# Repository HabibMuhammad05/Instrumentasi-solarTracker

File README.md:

# Solar Tracker and Monitoring System

This project is a solar tracking and monitoring system designed to adjust the position of a solar panel based on light intensity and monitor several electrical and environmental parameters.

The system uses two microcontrollers, an Arduino Nano and an ESP8266. The Arduino Nano handles the tracking mechanism, sensor readings, and output controls, while the ESP8266 manages serial communication, Wi-Fi connectivity, data transmission, and the OLED display.

The repository contains several program versions and test examples from the development process. The latest program set available in this repository is **Arduino Nano V2.1** and **ESP8266 V2.2**.

## Main Features

- Automatic solar panel positioning based on four LDR sensors.
- Manual positioning control through serial commands.
- Horizontal and vertical panel movement using two servo motors.
- Solar panel voltage, current, and power monitoring.
- Battery voltage and estimated battery level monitoring.
- Panel temperature measurement.
- Control of two PJU lighting outputs.
- LED output effects for tree lighting.
- OLED display for system status and monitoring information.
- Wi-Fi connection and HTTP data transmission to a configured server.
- Serial communication between the Arduino Nano and ESP8266.

## System Overview

The system is divided into two main parts.

### Arduino Nano

The Arduino Nano is responsible for the hardware control and data acquisition:

- Reads four LDR sensors to determine the direction of the strongest light.
- Adjusts the solar panel position through pan and tilt servo motors.
- Supports automatic and manual tracking modes.
- Measures solar panel voltage and current.
- Calculates solar panel power.
- Reads battery voltage and estimates its percentage.
- Reads panel temperature using an LM35 sensor.
- Controls two PJU outputs and four additional LED outputs.
- Sends monitoring data to the ESP8266 and receives control data through serial communication.

### ESP8266 (Wemos D1)

The ESP8266 handles communication and monitoring functions:

- Exchanges telemetry and control data with the Arduino Nano through serial communication.
- Connects to a Wi-Fi network.
- Sends monitoring data to a configured HTTP server in JSON format.
- Displays system information through a 128×64 OLED display.

## Hardware Overview

The main hardware components used in the project include:

- Arduino Nano.
- ESP8266 / Wemos D1 mini.
- Solar panel.
- Four LDR sensors.
- Two servo motors for horizontal and vertical movement.
- Voltage sensing circuits for the solar panel and battery.
- Current sensor for solar panel current measurement.
- LM35 temperature sensor.
- 128×64 OLED display using the SSD1306 controller.
- PJU lighting outputs and additional LED indicators.
- Power supply, battery, wiring, and supporting electronic components.
- Custom PCB for system integration.

Component specifications and wiring may vary depending on the hardware assembly. Refer to the schematic, PCB files, and pin definitions included in the repository before building or modifying the system.

## Software and Libraries

The programs are developed using the Arduino IDE.

The main libraries used in the latest program set include:

- **Servo2** – controls the pan and tilt servo motors on the Arduino Nano.
- **SoftwareSerial** – provides serial communication between the Arduino Nano and ESP8266.
- **U8g2** – controls the SSD1306 OLED display.
- **ESP8266WiFi** – manages the ESP8266 Wi-Fi connection.
- **ESP8266HTTPClient** – handles HTTP requests to the server.
- **ArduinoJson** – formats monitoring data into JSON.

Some earlier programs and examples use additional libraries. Install the libraries required by the specific sketch before compiling it.

## Repository Contents

The repository contains several program versions and supporting files:

| Folder | Description |
|---|---|
| `ArduinoNano_DualComms` | Arduino Nano program for an earlier dual-communication development version. |
| `ArduinoNano_FixCode_Comms` | Revised Arduino Nano program with separated control and monitoring functions. |
| `ArduinoNano_V2.1_FixCode_Comms` | Latest Arduino Nano program included in this repository. |
| `Esp8266_DualComms` | ESP8266 program for an earlier dual-communication development version. |
| `Esp8266_FixCode_Comms` | Revised ESP8266 communication program. |
| `Esp8266_V2.1_FixCode_Comms` | ESP8266 program with earlier monitoring and communication features. |
| `Esp8266_V2.2_FixCode_Comms` | Latest ESP8266 program included in this repository. |
| `SolarTracker_Example` | Basic solar tracking program for testing the LDR sensors and servo motors. |
| `SolarTracker_VoltCurrent_Example` | Example combining solar tracking, electrical measurements, and lighting control. |
| `Libraries` | Supporting library archives used during development. |
| `Other Files & Documentation` | Schematics, PCB design files, pin definitions, and other project documentation. |

The latest program set uses the Arduino Nano V2.1 and ESP8266 V2.2 folders. The older versions and standalone examples are retained as references and should not be mixed with the latest program files unless their compatibility has been checked.

## Getting Started

1. Install the Arduino IDE.
2. Install Arduino Nano and ESP8266 board support.
3. Install the libraries required by each program.
4. Download or clone this repository.
5. Open `ArduinoNano_V2.1_FixCode_Comms.ino` from the `ArduinoNano_V2.1_FixCode_Comms` folder.
6. Open `Esp8266_V2.2_FixCode_Comms.ino` from the `Esp8266_V2.2_FixCode_Comms` folder.
7. Select the correct board and port for each microcontroller.
8. Check the pin assignments, wiring, and communication connections.
9. Configure the Wi-Fi network and server address in the ESP8266 source files.
10. Compile and upload each program to its corresponding board.

Keep each sketch and its associated header files in the same folder. The Arduino Nano and ESP8266 programs must be uploaded separately to their respective boards.

## Configuration

Before operating the system, check the following settings:

- **Pin assignments:** Refer to the source code and `pn-Definitions.txt` in `Other Files & Documentation`.
- **Servo positions:** Check the pan and tilt limits in `SolarTracker.h`.
- **Tracking response:** Adjust the dead zone, movement step, and sensor smoothing settings to suit the mechanical assembly and lighting conditions.
- **Wi-Fi connection:** Set the correct SSID and password in the ESP8266 program.
- **Server address:** Update `serverName` in `GlobalVariables.h` to match the HTTP endpoint used by the monitoring server.
- **Sensor calibration:** Verify voltage and current readings against appropriate measuring instruments before using the displayed values.

## Hardware Documentation

Additional hardware design files are available in `Other Files & Documentation`, including:

- PCB layout and board files.
- Circuit schematic files.
- Schematic PDF documents.
- Pin definition reference.

These files can be used as references when assembling, checking, or modifying the hardware.

## Notes

- The latest program set in this repository is Arduino Nano V2.1 and ESP8266 V2.2.
- The Arduino Nano and ESP8266 use separate sketches and communicate through a serial connection.
- The ESP8266 requires a working Wi-Fi network and a reachable server endpoint for HTTP data transmission.
- Sensor readings and calculated electrical values should be calibrated according to the actual sensor modules and circuit configuration.
- Servo movement limits and tracking parameters may need adjustment based on the mechanical design.
- Check the power requirements of the servo motors, lighting outputs, and microcontroller boards before connecting the system.

---

This repository contains the source code and supporting design files for the development of the Solar Tracker and Monitoring System.

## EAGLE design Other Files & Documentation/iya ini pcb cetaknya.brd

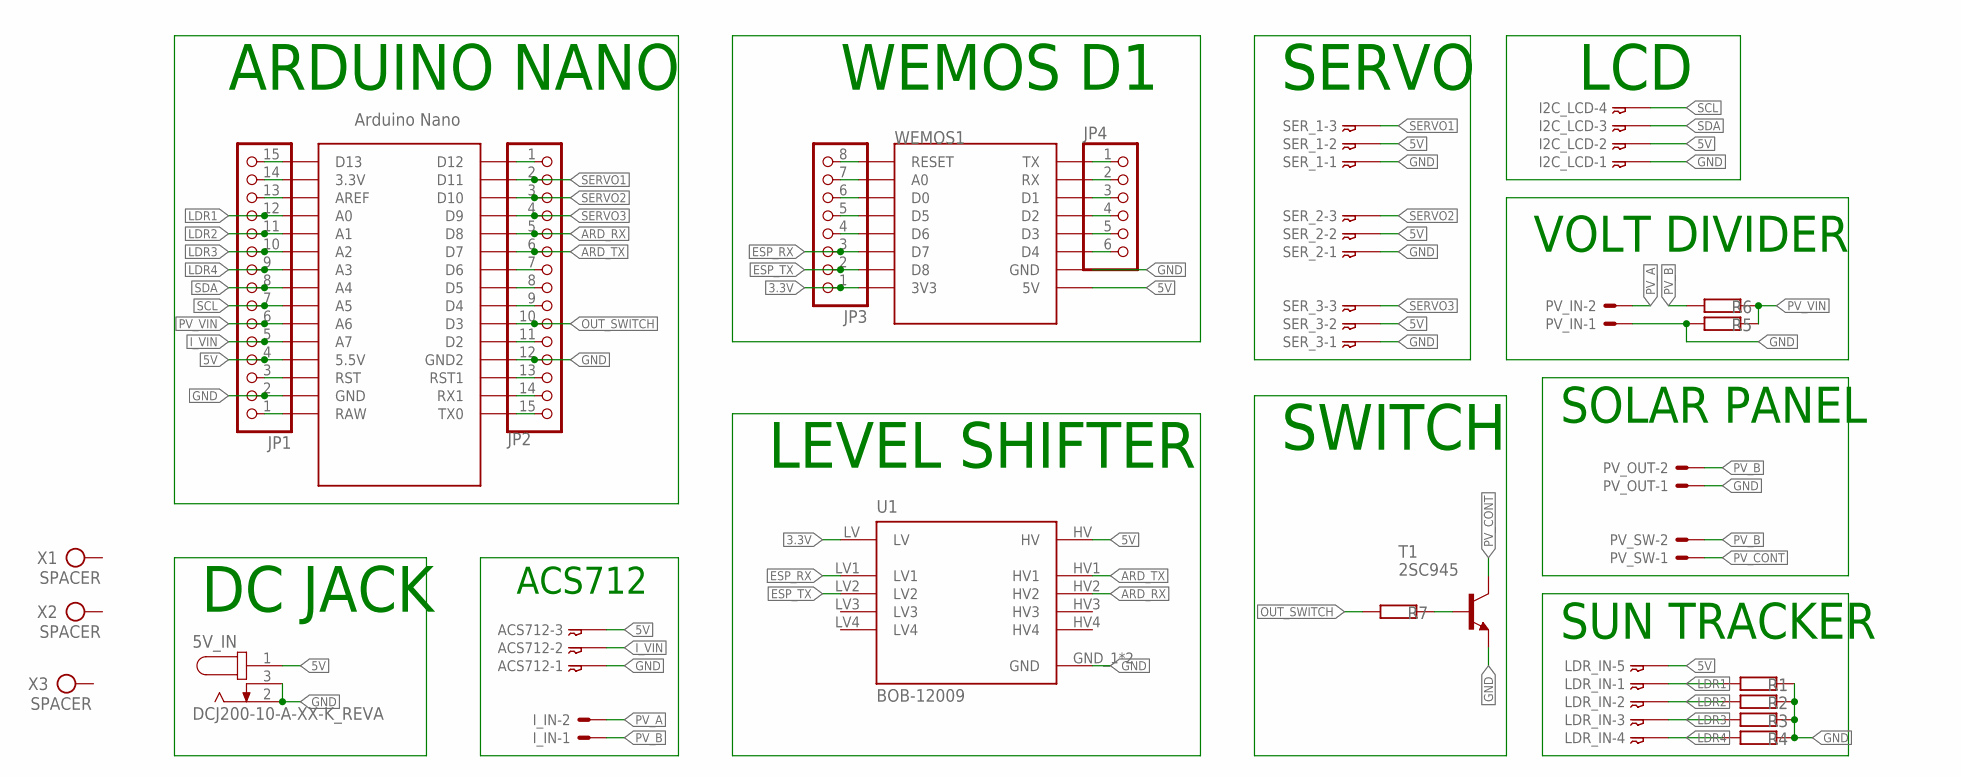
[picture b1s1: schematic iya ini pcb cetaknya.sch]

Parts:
5V_IN: DCJ200-10-A-XX-K_REVA; GCT_DCJ200-10-A-XX-K_REVA
ACS712: 03-JST-B3B-XH-A; B3B-XH
I2C_LCD: 04-JST-B4B-XH-A; B4B-XH
I_IN: MOLEX_2P_27-2021; 6410-02
JP1, JP2: PINHD-1X15; 1X15
JP3: PINHD-1X8; 1X08
JP4: PINHD-1X6; 1X06
LDR_IN: 05-JST-B5B-XH-A; B5B-XH
PV_IN: MOLEX_2P_27-2021; 6410-02
PV_OUT: MOLEX_2P_27-2021; 6410-02
PV_SW: MOLEX_2P_27-2021; 6410-02
R1, R2, R3, R4: R-EU_0207/2V; 0207/2V
R5, R6, R7: R-EU_0207/10; 0207/10
SER_1, SER_2, SER_3: 03-JST-B3B-XH-A; B3B-XH
T1: 2SC945; TO92-ECB
U1: BOB-12009; CONV_BOB-12009
U$1: NANO
WEMOS1: WEMOS-D1-MINI
X1, X2, X3: SPACER

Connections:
3.3V: JP3.1, U1.LV, WEMOS1.3V3
5V: 5V_IN.1, ACS712.P$3, I2C_LCD.P$2, JP1.4, LDR_IN.P$5, SER_1.P$2, SER_2.P$2, SER_3.P$2, U1.HV, U$1.5V (5.5V), WEMOS1.5V
ARD_RX: JP2.5, U1.HV2, U$1.D8
ARD_TX: JP2.6, U1.HV1, U$1.D7
ESP_RX: JP3.3, U1.LV1, WEMOS1.D7
ESP_TX: JP3.2, U1.LV2, WEMOS1.D8
GND: 5V_IN.2, 5V_IN.3, ACS712.P$1, I2C_LCD.P$1, JP1.2, JP2.12, PV_IN.1, PV_OUT.1, R1.2, R2.2, R3.2, R4.2, R5.1, SER_1.P$1, SER_2.P$1, SER_3.P$1, T1.E, U1.GND_1 (GND), U1.GND_2 (GND), U$1.GND, U$1.GND1 (GND2), WEMOS1.GND
I_VIN: ACS712.P$2, JP1.5, U$1.A7
LDR1: JP1.12, LDR_IN.P$1, R1.1, U$1.A0
LDR2: JP1.11, LDR_IN.P$2, R2.1, U$1.A1
LDR3: JP1.10, LDR_IN.P$3, R3.1, U$1.A2
LDR4: JP1.9, LDR_IN.P$4, R4.1, U$1.A3
unnamed: JP2.7, U$1.D6
unnamed: R7.2, T1.B
unnamed: JP2.1, U$1.D12
unnamed: JP3.8, WEMOS1.RESET
unnamed: JP3.7, WEMOS1.A0
unnamed: JP2.8, U$1.D5
unnamed: JP2.9, U$1.D4
unnamed: JP3.6, WEMOS1.D0
unnamed: JP2.11, U$1.D2
unnamed: JP3.5, WEMOS1.D5
unnamed: JP2.13, U$1.RST1
unnamed: JP2.14, U$1.RX1
unnamed: JP2.15, U$1.TX0
unnamed: JP1.1, U$1.RAW
unnamed: JP1.3, U$1.RST
unnamed: JP3.4, WEMOS1.D6
unnamed: JP1.13, U$1.AREF
unnamed: JP1.14, U$1.3.3V
unnamed: JP1.15, U$1.D13
unnamed: JP4.6, WEMOS1.D4
unnamed: JP4.5, WEMOS1.D3
unnamed: JP4.4, WEMOS1.D2
unnamed: JP4.3, WEMOS1.D1
unnamed: JP4.2, WEMOS1.RX
unnamed: JP4.1, WEMOS1.TX
OUT_SWITCH: JP2.10, R7.1, U$1.D3
PV_A: I_IN.2, PV_IN.2
PV_B: I_IN.1, PV_OUT.2, PV_SW.2, R6.1
PV_CONT: PV_SW.1, T1.C
PV_VIN: JP1.6, R5.2, R6.2, U$1.A6
SCL: I2C_LCD.P$4, JP1.7, U$1.A5
SDA: I2C_LCD.P$3, JP1.8, U$1.A4
SERVO1: JP2.2, SER_1.P$3, U$1.D11
SERVO2: JP2.3, SER_2.P$3, U$1.D10
SERVO3: JP2.4, SER_3.P$3, U$1.D9

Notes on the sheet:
ARDUINO NANO
WEMOS D1
SERVO
LCD
DC JACK
ACS712
LEVEL SHIFTER
SWITCH
SOLAR PANEL
SUN TRACKER
VOLT DIVIDER

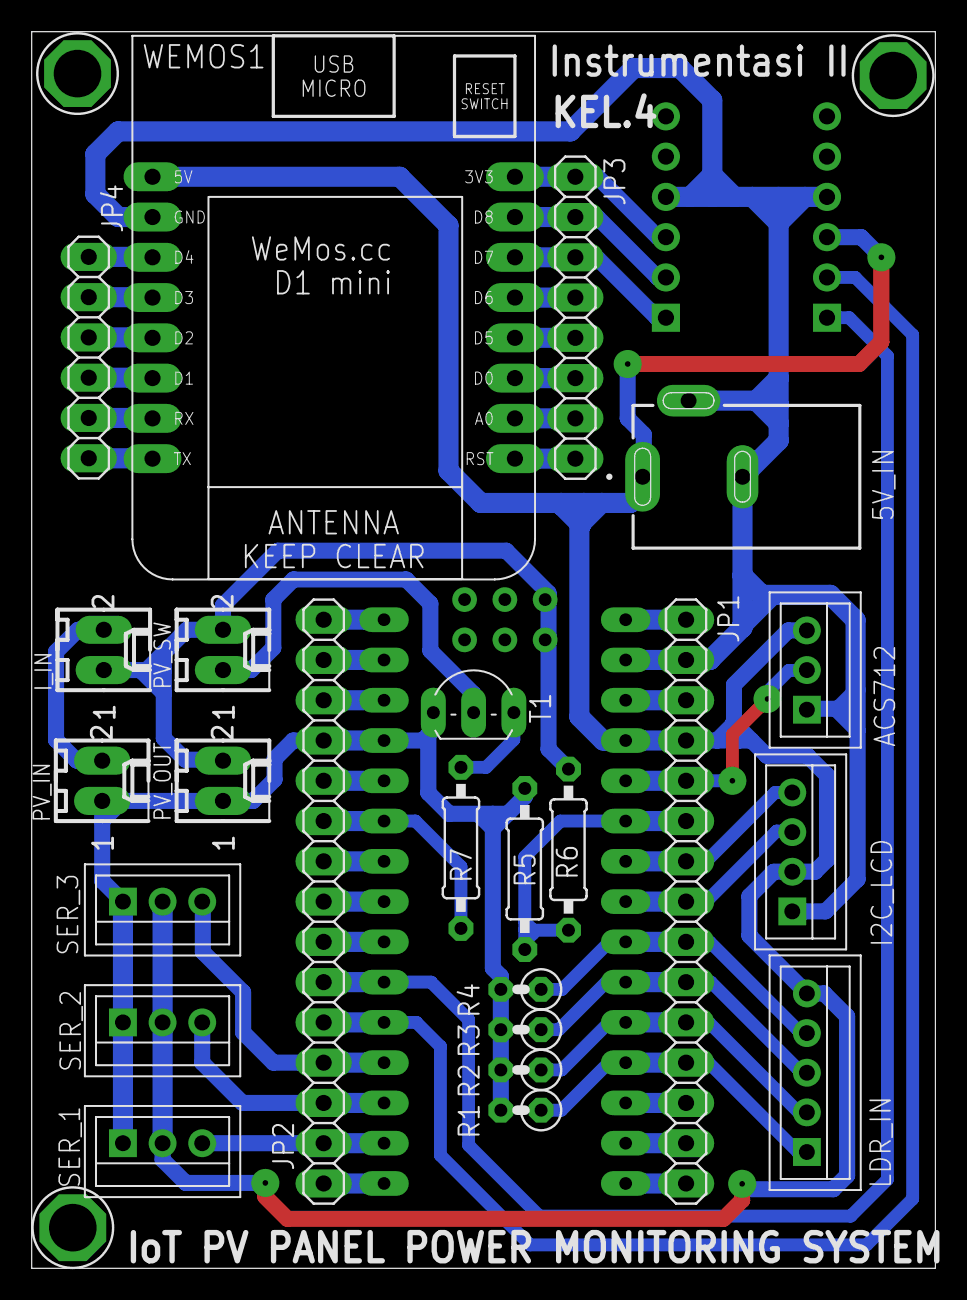
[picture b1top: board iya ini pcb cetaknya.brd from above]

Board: 2 copper layers, 57.0 x 78.0 mm, 29 parts (1 on the bottom side), 47 nets.

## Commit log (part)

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2025-12-13 added first Code
2025-12-13 added documentation
2025-12-13 added PinDef
2025-12-13 added libraries
2025-12-17 updated last code
